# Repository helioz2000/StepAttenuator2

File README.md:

# StepAttenuator2
### Step Attenuator for Marconi 2955

To replace the original electro-mechanical Step Attenuator which suffers from wear of electro-mechnical components. 

The board is mechanically compatible with the original Marconi step attenuator 

The MCU is normally in deep sleep mode (no clock) to prevent interference. It only wakes up when the MI2955 issues a command to change the attenuation setting.

The board design allows for the MCU section to be separated from the attenuator to be located in a different housing if desired.

[Circuit PDF](Doc/StepAttenuatorCircuit.pdf)

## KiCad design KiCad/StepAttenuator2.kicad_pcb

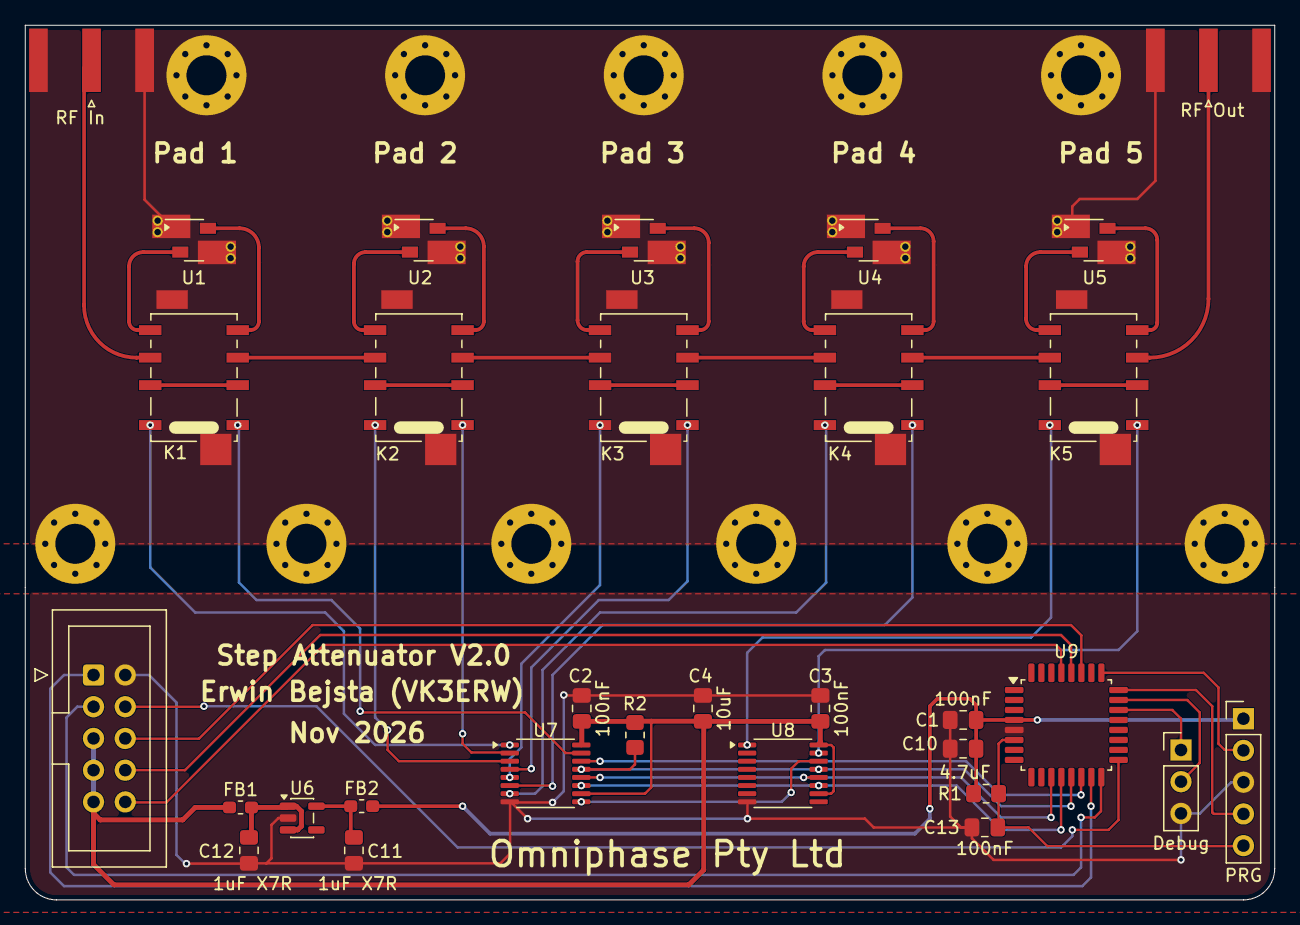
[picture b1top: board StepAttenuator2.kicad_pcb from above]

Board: 4 copper layers, 100.0 x 70.0 mm, 42 parts (0 on the bottom side), 52 nets.

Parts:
C1, C2, C3, C13: 100nF; C_0805_2012Metric_Pad1.18x1.45mm_HandSolder
C4: 10uF; C_0805_2012Metric_Pad1.18x1.45mm_HandSolder
C10: 4.7uF; C_0805_2012Metric_Pad1.18x1.45mm_HandSolder
C11, C12: 1uF X7R; C_0805_2012Metric_Pad1.18x1.45mm_HandSolder
FB1, FB2: MH1608A-301Y; L_0603_1608Metric_Pad1.05x0.95mm_HandSolder
GND: MountingHole_3.2mm_M3_Pad_Via
GND#2, GND#3, GND#4, GND#5, GND#6, GND#7, GND#8, GND#9, GND#10, GND#11: MountingHole_3.2mm_M3_Pad_Via
J3: RF In; SMA_Amphenol_132289_EdgeMount
J4: RF Out; SMA_Amphenol_132289_EdgeMount
J5: MI2955; IDC-Header_2x05_P2.54mm_Vertical
J6: PRG; PinHeader_1x05_P2.54mm_Vertical
J7: Debug; PinHeader_1x03_P2.54mm_Vertical
K1, K2, K3, K4, K5: G6KU-2RF-S DC5; Relay_DPDT_Omron_G6K-2F-RF_special
R1, R2: 10K; R_0805_2012Metric_Pad1.20x1.40mm_HandSolder
U1, U2, U3, U4, U5: LAT-20+; Mini-Circuits_MMM168_LandPatternPL-225
U6: TPS7A2033PDBVR; SOT-23-5
U7, U8: SN74ACT595; TSSOP-16_4.4x5mm_P0.65mm
U9: STM32G030K8T6; LQFP-32_7x7mm_P0.8mm

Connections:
+3.3V: C1.1, C10.1, FB2.2, J6.1, R1.1, U9.4 (VDD)
+5V: C2.1, C3.1, C4.1, FB1.1, J5.5, J5.7, J5.9, R2.1, U7.10 (~SRCLR), U7.16 (VCC), U8.10 (~SRCLR), U8.16 (VCC)
/StepAttenuator2/20dB In: J5.4, U9.17 (PB2)
/StepAttenuator2/20dB Out: J5.6, U9.27 (PB3)
/StepAttenuator2/40dB In a: J5.1, U9.15 (PB0)
/StepAttenuator2/40dB In b: J5.8, U9.28 (PB4)
/StepAttenuator2/40dB Out a: J5.3, U9.16 (PB1)
/StepAttenuator2/40dB Out b: J5.10, U9.29 (PB5)
/StepAttenuator2/NRST: C13.2, J6.5, R1.2, U9.6 (NRST)
/StepAttenuator2/SWCLK: J6.2, U9.25 (SYS_SWCLK)
/StepAttenuator2/SWDIO: J6.4, U9.24 (SYS_SWDIO)
GND: C1.2, C2.2, C3.2, C4.2, C10.2, C11.2, C12.2, C13.1, GND.1, GND#2.1, GND#3.1, GND#4.1, GND#5.1, GND#6.1, GND#7.1, GND#8.1, GND#9.1, GND#10.1, GND#11.1, J3.2 (Ext), J4.2 (Ext), J5.2, J6.3, J7.3, K1.9 (Shield_9), K2.9 (Shield_9), K3.9 (Shield_9), K4.9 (Shield_9), K5.9 (Shield_9), U1.1 (GND), U1.3 (GND), U2.1 (GND), U2.3 (GND), U3.1 (GND), U3.3 (GND), U4.1 (GND), U4.3 (GND), U5.1 (GND), U5.3 (GND), U6.2 (GND), U7.8 (GND), U8.8 (GND), U9.5 (VSS)
K1R: K1.8, U7.1 (QB)
K1S: K1.1, U7.15 (QA)
K2R: K2.8, U7.3 (QD)
K2S: K2.1, U7.2 (QC)
K3R: K3.8, U7.5 (QF)
K3S: K3.1, U7.4 (QE)
K4R: K4.8, U7.7 (QH)
K4S: K4.1, U7.6 (QG)
K5R: K5.8, U8.1 (QB)
K5S: K5.1, U8.15 (QA)
unnamed: J3.1 (In), K1.6
unnamed: J4.1 (In), K5.3
unnamed: J7.1, U9.22 (PA9/PA11)
unnamed: J7.2, U9.23 (PA10/PA12)
unnamed: K1.2, K1.7
unnamed: K1.3, K2.6
unnamed: K2.2, K2.7
unnamed: K2.3, K3.6
unnamed: K3.2, K3.7
unnamed: K3.3, K4.6
unnamed: K4.2, K4.7
unnamed: K4.3, K5.6
unnamed: K5.2, K5.7
unnamed: K1.5, U1.4 (IN)
unnamed: K1.4, U1.2 (OUT)
unnamed: K2.5, U2.4 (IN)
unnamed: K2.4, U2.2 (OUT)
unnamed: K3.5, U3.4 (IN)
unnamed: K3.4, U3.2 (OUT)
unnamed: K4.5, U4.4 (IN)
unnamed: K4.4, U4.2 (OUT)
unnamed: K5.5, U5.4 (IN)
unnamed: K5.4, U5.2 (OUT)
unnamed: C12.1, FB1.2, U6.1 (IN), U6.3 (EN)
unnamed: C11.1, FB2.1, U6.5 (OUT)
unnamed: U7.9 (QH'), U8.14 (SER)
unnamed: U7.12 (RCLK), U8.12 (RCLK), U9.11 (PA4)
unnamed: U7.14 (SER), U9.14 (PA7)
unnamed: U7.11 (SRCLK), U8.11 (SRCLK), U9.12 (PA5)
unnamed: R2.2, U7.13 (~OE), U8.13 (~OE), U9.13 (PA6)
